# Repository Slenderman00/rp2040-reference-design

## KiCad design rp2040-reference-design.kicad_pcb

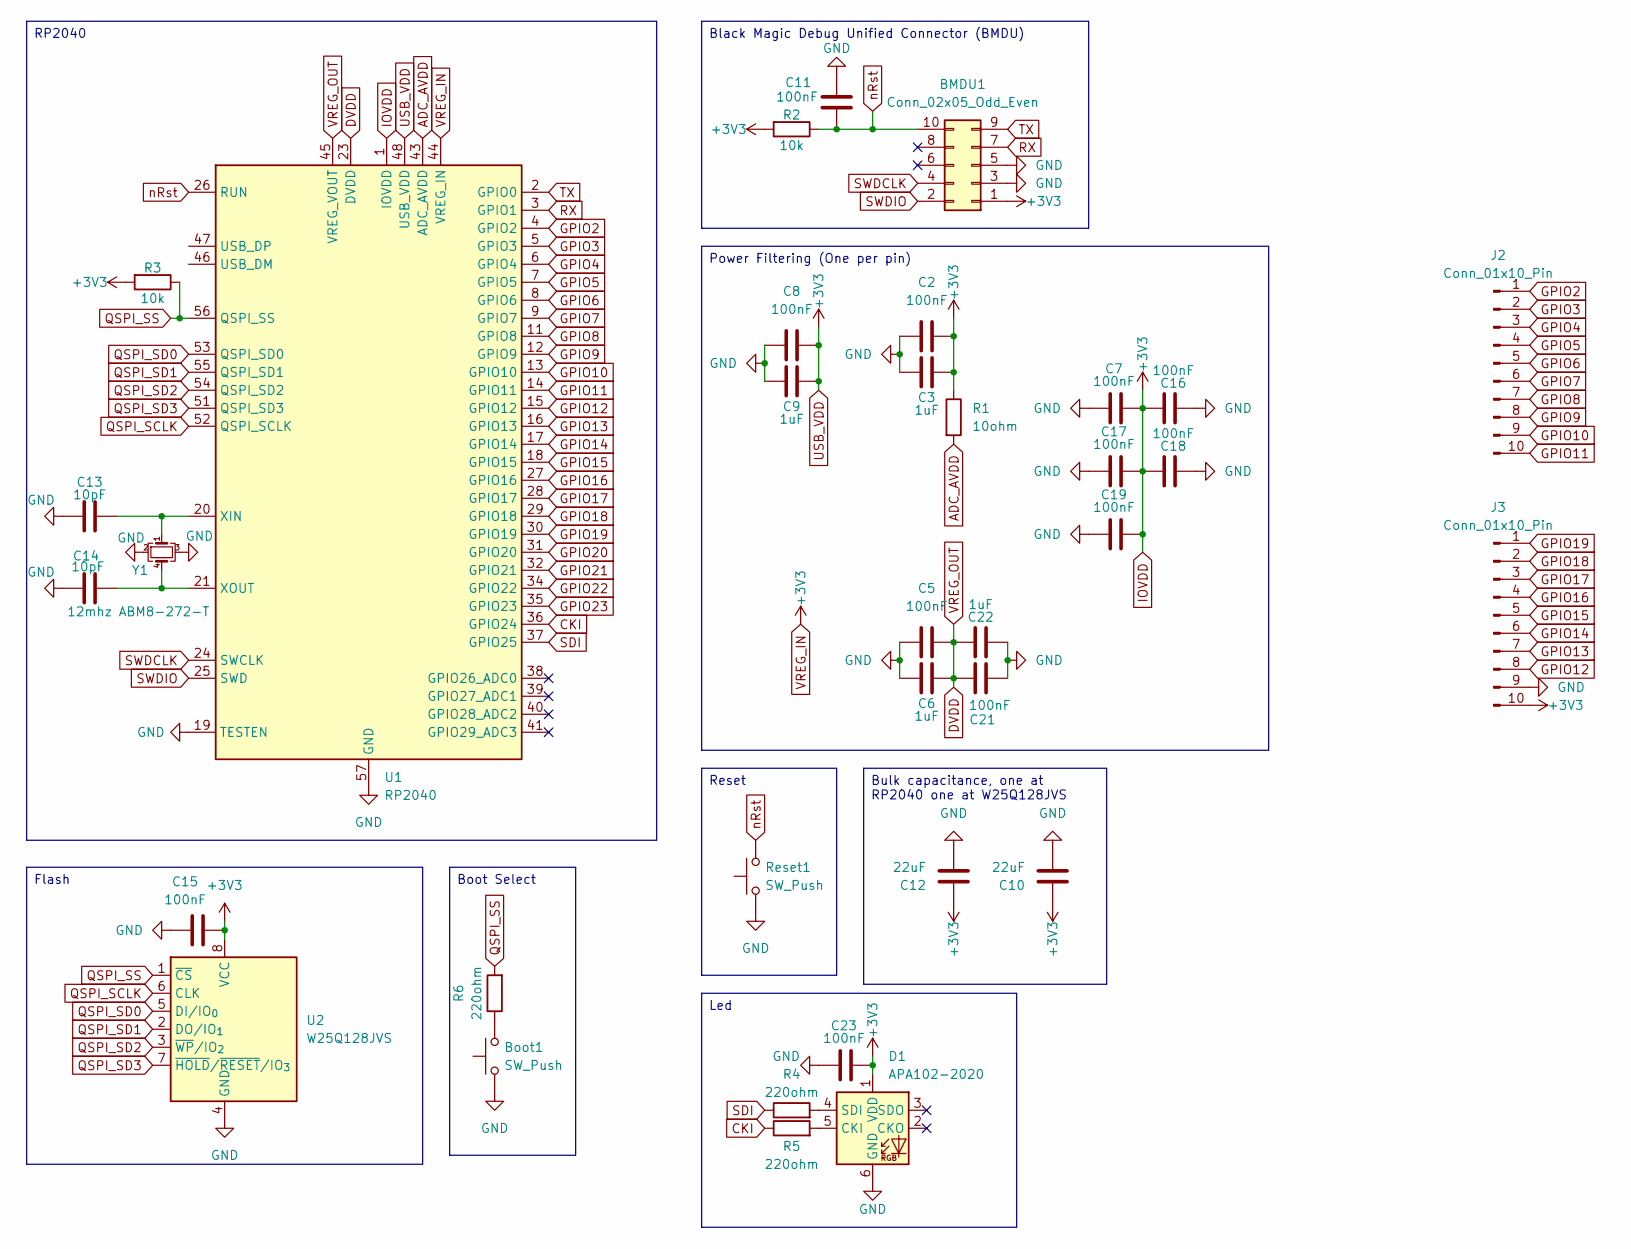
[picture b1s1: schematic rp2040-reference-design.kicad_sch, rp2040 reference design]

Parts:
BMDU1: Conn_02x05_Odd_Even; PinHeader_2x05_P1.27mm_Vertical_SMD
Boot1: SW_Push; SW_SPST_EVQP7A
C2, C5, C7, C8, C11, C15, C16, C17, C18, C19, C21, C23: 100nF; C_0402_1005Metric
C3, C6, C9, C22: 1uF; C_0402_1005Metric
C10, C12: 22uF; C_0402_1005Metric
C13, C14: 10pF; C_0402_1005Metric
D1: APA102-2020; LED-APA102-2020
J2, J3: Conn_01x10_Pin; PinSocket_1x10_P2.54mm_Vertical
R1: 10ohm; R_0402_1005Metric
R2, R3: 10k; R_0402_1005Metric
R4, R5, R6: 220ohm; R_0402_1005Metric
Reset1: SW_Push; SW_SPST_EVQP7A
U1: RP2040; QFN-56-1EP_7x7mm_P0.4mm_EP3.2x3.2mm
U2: W25Q128JVS; SOIC-8_5.3x5.3mm_P1.27mm
Y1: 12mhz ABM8-272-T; ABRACON ABM8-272-T3

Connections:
ADC_AVDD: R1.2, U1.43 (ADC_AVDD)
CKI: R5.1, U1.36 (GPIO24)
DVDD: C5.2, C6.2, C21.2, C22.2, U1.23 (DVDD), U1.45 (VREG_VOUT), U1.50 (DVDD)
GND: BMDU1.3, BMDU1.5, Boot1.1, C2.1, C3.1, C5.1, C6.1, C7.1, C8.1, C9.1, C10.2, C11.1, C12.2, C13.1, C14.1, C15.1, C16.1, C17.1, C18.1, C19.1, C21.1, C22.1, C23.1, D1.6 (GND), J3.9, Reset1.1, U1.19 (TESTEN), U1.57 (GND), U2.4 (GND), Y1.2, Y1.3
GPIO2: J2.1, U1.4 (GPIO2)
GPIO3: J2.2, U1.5 (GPIO3)
GPIO4: J2.3, U1.6 (GPIO4)
GPIO5: J2.4, U1.7 (GPIO5)
GPIO6: J2.5, U1.8 (GPIO6)
GPIO7: J2.6, U1.9 (GPIO7)
GPIO8: J2.7, U1.11 (GPIO8)
GPIO9: J2.8, U1.12 (GPIO9)
GPIO10: J2.9, U1.13 (GPIO10)
GPIO11: J2.10, U1.14 (GPIO11)
GPIO12: J3.8, U1.15 (GPIO12)
GPIO13: J3.7, U1.16 (GPIO13)
GPIO14: J3.6, U1.17 (GPIO14)
GPIO15: J3.5, U1.18 (GPIO15)
GPIO16: J3.4, U1.27 (GPIO16)
GPIO17: J3.3, U1.28 (GPIO17)
GPIO18: J3.2, U1.29 (GPIO18)
GPIO19: J3.1, U1.30 (GPIO19)
GPIO20: U1.31 (GPIO20)
GPIO21: U1.32 (GPIO21)
GPIO22: U1.34 (GPIO22)
GPIO23: U1.35 (GPIO23)
IOVDD: BMDU1.1, C2.2, C3.2, C7.2, C8.2, C9.2, C10.1, C12.1, C15.2, C16.2, C17.2, C18.2, C19.2, C23.2, D1.1 (VDD), J3.10, R1.1, R2.2, R3.2, U1.1 (IOVDD), U1.10 (IOVDD), U1.22 (IOVDD), U1.33 (IOVDD), U1.42 (IOVDD), U1.44 (VREG_IN), U1.48 (USB_VDD), U1.49 (IOVDD), U2.8 (VCC)
unnamed: Boot1.2, R6.1
unnamed: D1.5 (CKI), R5.2
unnamed: D1.4 (SDI), R4.2
unnamed: C13.2, U1.20 (XIN), Y1.1
unnamed: C14.2, U1.21 (XOUT), Y1.4
QSPI_SCLK: U1.52 (QSPI_SCLK), U2.6 (CLK)
QSPI_SD0: U1.53 (QSPI_SD0), U2.5 (DI/IO_{0})
QSPI_SD1: U1.55 (QSPI_SD1), U2.2 (DO/IO_{1})
QSPI_SD2: U1.54 (QSPI_SD2), U2.3 (~WP/IO_{2})
QSPI_SD3: U1.51 (QSPI_SD3), U2.7 (~HOLD/~RESET/IO_{3})
QSPI_SS: R3.1, R6.2, U1.56 (QSPI_SS), U2.1 (~CS)
RX: BMDU1.7, U1.3 (GPIO1)
SDI: R4.1, U1.37 (GPIO25)
SWDCLK: BMDU1.4, U1.24 (SWCLK)
SWDIO: BMDU1.2, U1.25 (SWD)
TX: BMDU1.9, U1.2 (GPIO0)
nRst: BMDU1.10, C11.2, R2.1, Reset1.2, U1.26 (RUN)

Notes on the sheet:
Black Magic Debug Unified Connector (BMDU)
Led
Bulk capacitance, one at RP2040 one at W25Q128JVS
Power Filtering (One per pin)
Reset
Flash
Boot Select
RP2040

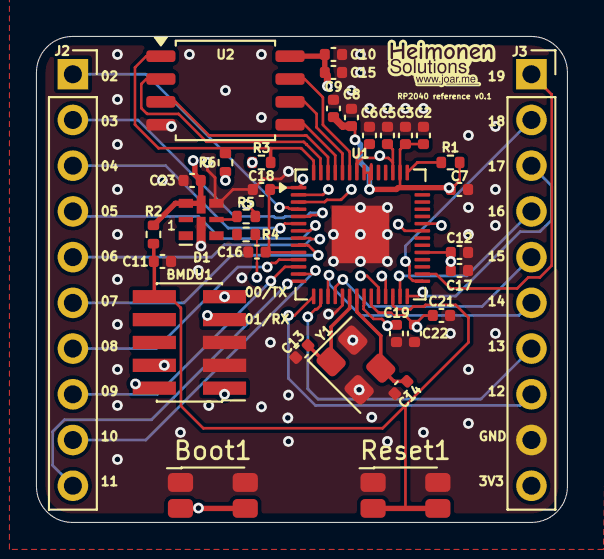
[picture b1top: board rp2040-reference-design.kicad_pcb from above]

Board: 4 copper layers, 29.5 x 27.0 mm, 35 parts (0 on the bottom side), 40 nets.

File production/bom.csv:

Designator,Footprint,Quantity,Value,LCSC Part #
BMDU,PinHeader_2x05_P1.27mm_Vertical_SMD,1,Conn_02x05_Odd_Even,
"BOOT, RESET",SW_SPST_EVQP7A,2,SW_Push,
"C10, C12",0402,2,22uF,
"C11, C15, C16, C17, C18, C19, C2, C21, C23, C5, C7, C8",0402,12,100nF,
"C13, C14",0402,2,10pF,
"C22, C3, C6, C9",0402,4,1uF,
D1,LED-APA102-2020,1,APA102-2020,
"J2, J3",PinSocket_1x10_P2.54mm_Vertical,2,Conn_01x10_Pin,
R1,0402,1,10ohm,
"R2, R3",0402,2,10k,
"R4, R5, R6",0402,3,220ohm,
U1,QFN-56-1EP_7x7mm_P0.4mm_EP3.2x3.2mm,1,RP2040,
U2,SOIC-8_5.3x5.3mm_P1.27mm,1,W25Q128JVS,
Y1,Crystal_SMD_3225-4Pin_3.2x2.5mm,1,12mhz ABM8-272-T,

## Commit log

2025-12-29 feat: initial reference design
2025-12-29 fix: one cap per pin
2025-12-29 feat: led
2025-12-29 fix: connectec uart
2025-12-29 fix: connected vref
2025-12-30 feat: reference layout
2025-12-30 fix: drc
2025-12-30 fix: button text
2026-01-02 feat: added pin numbers
2026-01-02 feat: removed traces from underside of clock
2026-01-02 fix: removed unused via
2026-01-02 feat: small improvements
2026-01-02 fix: drc problems
2026-01-03 feat: did stuff
2026-01-03 feat: annotated stuff
2026-01-03 feat: changes
2026-01-16 fix: grounded cap
2026-01-16 fix: more stitching
2026-01-26 fix: mcorrected crystal pinout
2026-01-26 feat: fixed silkscreen stuff
